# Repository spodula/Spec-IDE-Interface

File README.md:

# Spec-IDE-Interface
Buffered and Unbuffered 8 bit IDE interfaces for the zx Spectrum.

This is a (Another) remake of the Pera Putnik/Gary Lancaster design for a simple 8-bit IDE interface for the zx Spectrum.

There are two versions of this, and unbuffered version which is basically the same as the PP/GL design except with additional HDD and Power LED pins.

The Buffered one buffers all the lines going to the Hard drive, which should make the interface more reliable for longer cable lengths.

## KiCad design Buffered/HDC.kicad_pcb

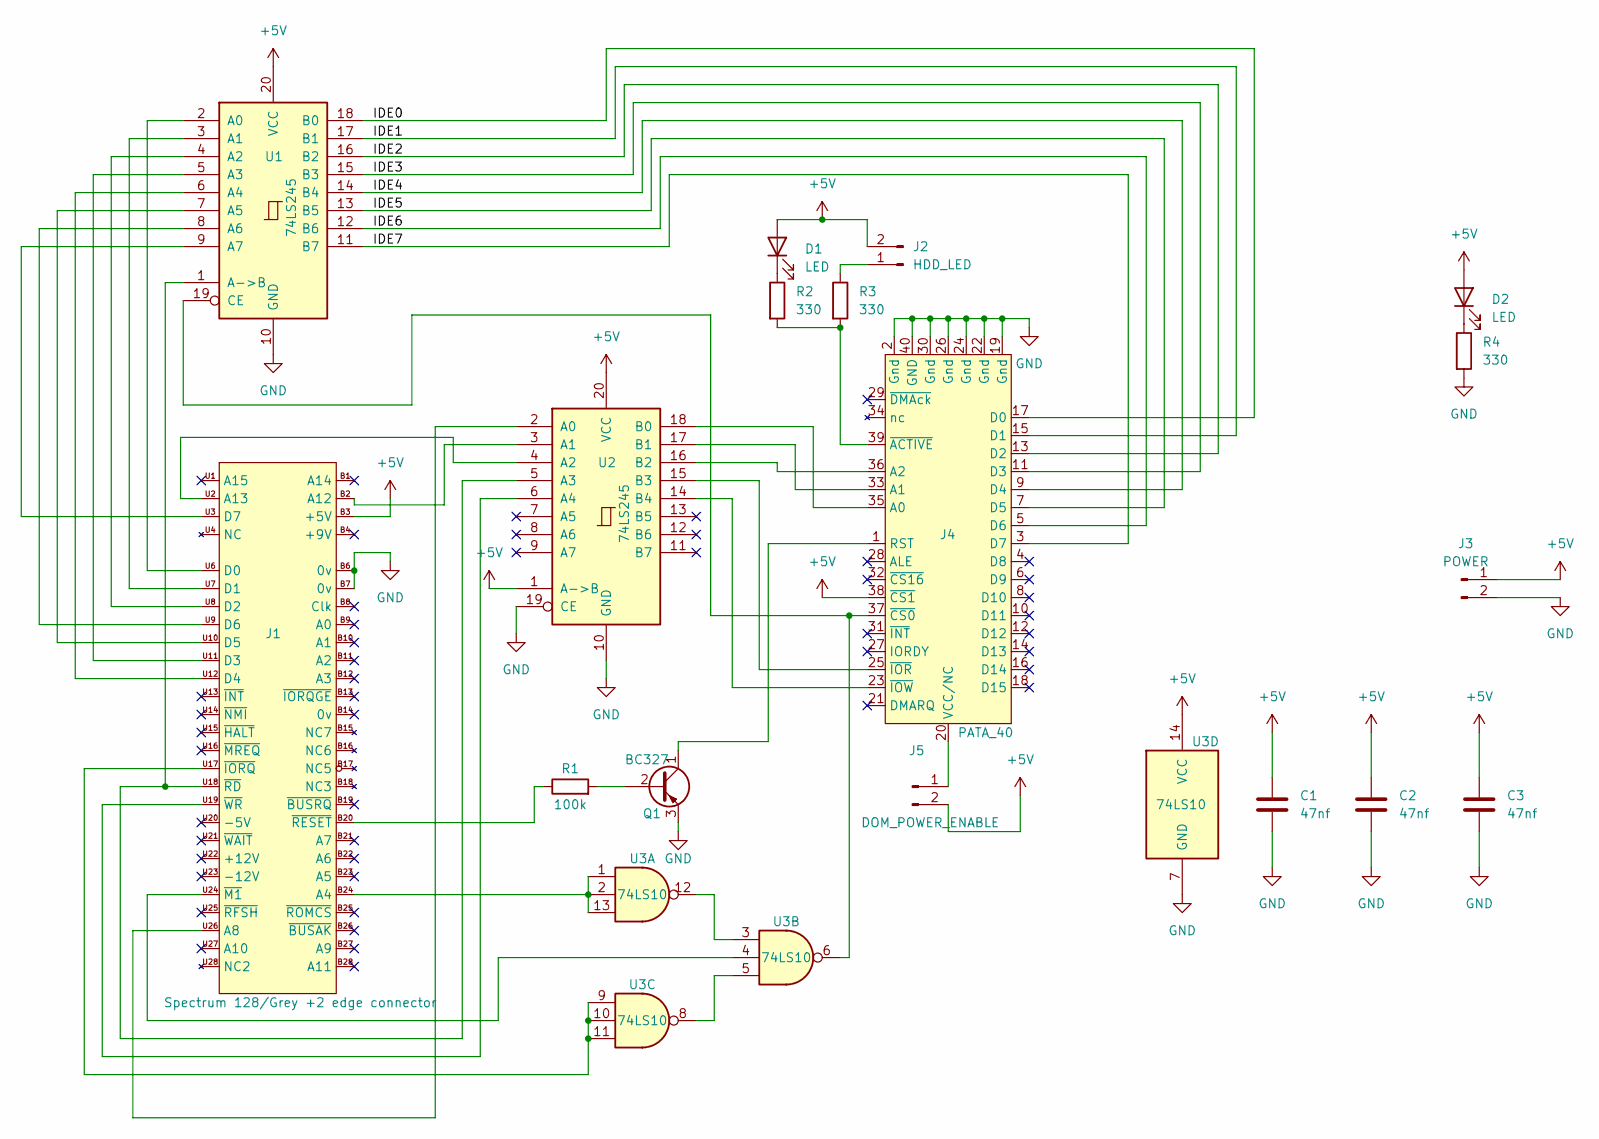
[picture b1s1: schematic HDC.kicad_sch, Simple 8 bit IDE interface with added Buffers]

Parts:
C1, C2, C3: 47nf; C_Disc_D3.0mm_W1.6mm_P2.50mm
D1, D2: LED; LED_D5.0mm
J1: Spectrum 128/Grey +2 edge connector; Speccy_edge_External
J2: HDD_LED; PinHeader_1x02_P2.54mm_Horizontal
J3: POWER; PinHeader_1x02_P2.54mm_Horizontal
J4: PATA_40; PinHeader_2x20_P2.54mm_Vertical
J5: DOM_POWER_ENABLE; PinHeader_1x02_P2.54mm_Horizontal
Q1: BC327; TO-92_Inline
R1: 100k; R_Axial_DIN0207_L6.3mm_D2.5mm_P7.62mm_Horizontal
R2, R3, R4: 330; R_Axial_DIN0207_L6.3mm_D2.5mm_P7.62mm_Horizontal
U1, U2: 74LS245; DIP-20_W7.62mm_LongPads
U3: 74LS10; DIP-14_W7.62mm_LongPads

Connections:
+5V: C1.1, C2.1, C3.1, D1.2 (A), D2.2 (A), J1.B3 (+5V), J2.2, J3.1, J4.38 (~CS1), J5.2, U1.20 (VCC), U2.1 (A->B), U2.20 (VCC), U3.14 (VCC)
/IDE0: J4.17 (D0), U1.18 (B0)
/IDE1: J4.15 (D1), U1.17 (B1)
/IDE2: J4.13 (D2), U1.16 (B2)
/IDE3: J4.11 (D3), U1.15 (B3)
/IDE4: J4.9 (D4), U1.14 (B4)
/IDE5: J4.7 (D5), U1.13 (B5)
/IDE6: J4.5 (D6), U1.12 (B6)
/IDE7: J4.3 (D7), U1.11 (B7)
GND: C1.2, C2.2, C3.2, J1.B6 (0v), J1.B7 (0v), J3.2, J4.2 (Gnd), J4.19 (Gnd), J4.22 (Gnd), J4.24 (Gnd), J4.26 (Gnd), J4.30 (Gnd), J4.40 (GND), Q1.3 (E), R4.2, U1.10 (GND), U2.10 (GND), U2.19 (CE), U3.7 (GND)
unnamed: D1.1 (K), R2.1
unnamed: D2.1 (K), R4.1
unnamed: J1.B2 (A12), U2.3 (A1)
unnamed: J1.B20 (~RESET), R1.1
unnamed: J1.B24 (A4), U3.1, U3.2, U3.13
unnamed: J1.U2 (A13), U2.4 (A2)
unnamed: J1.U3 (D7), U1.9 (A7)
unnamed: J1.U6 (D0), U1.2 (A0)
unnamed: J1.U7 (D1), U1.3 (A1)
unnamed: J1.U8 (D2), U1.4 (A2)
unnamed: J1.U9 (D6), U1.8 (A6)
unnamed: J1.U10 (D5), U1.7 (A5)
unnamed: J1.U11 (D3), U1.5 (A3)
unnamed: J1.U12 (D4), U1.6 (A4)
unnamed: J1.U17 (~IORQ), U3.9, U3.10, U3.11
unnamed: J1.U18 (~RD), U1.1 (A->B), U2.5 (A3)
unnamed: J1.U19 (~WR), U2.6 (A4)
unnamed: J1.U24 (~M1), U3.4
unnamed: J1.U26 (A8), U2.2 (A0)
unnamed: J2.1, R3.1
unnamed: J4.1 (RST), Q1.1 (C)
unnamed: J4.20 (VCC/NC), J5.1
unnamed: J4.23 (~IOW), U2.14 (B4)
unnamed: J4.25 (~IOR), U2.15 (B3)
unnamed: J4.33 (A1), U2.17 (B1)
unnamed: J4.35 (A0), U2.18 (B0)
unnamed: J4.36 (A2), U2.16 (B2)
unnamed: J4.37 (~CS0), U1.19 (CE), U3.6
unnamed: J4.39 (~ACTIVE), R2.2, R3.2
unnamed: Q1.2 (B), R1.2
unnamed: U3.5, U3.8
unnamed: U3.3, U3.12

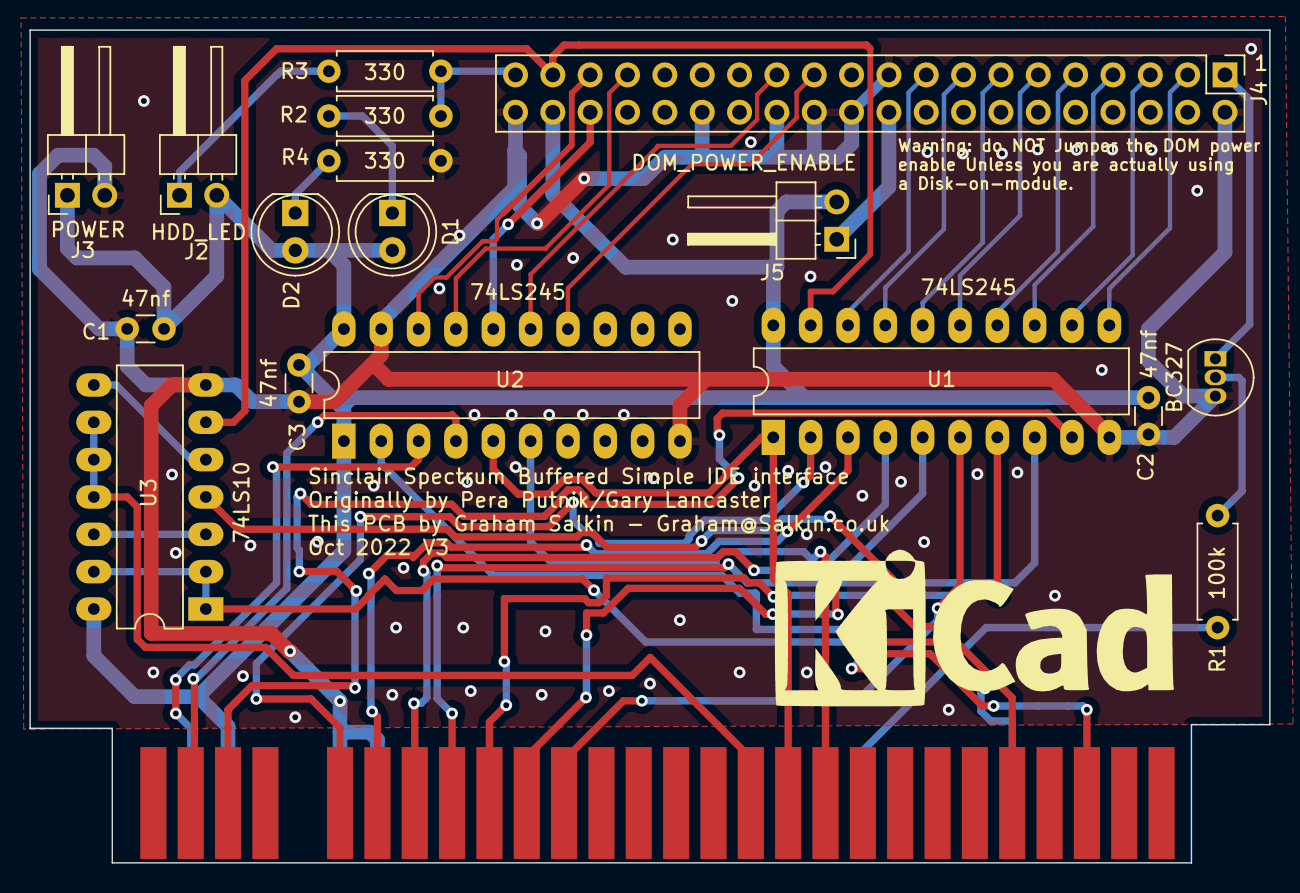
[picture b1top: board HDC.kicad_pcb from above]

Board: 2 copper layers, 84.3 x 56.6 mm, 18 parts (0 on the bottom side), 42 nets.

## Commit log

2022-11-13 Initial login
2022-11-13 Fixed the silk screen on the buffered version to properly credit the original designers.
